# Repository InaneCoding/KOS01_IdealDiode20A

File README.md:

20A 5V-60V Ideal Diode PCB
Ideal Diode circuit based on the Linear Tech LT4359
By Kevin Bibby / http://www.inanecoding.co.uk
----------------------------------------------
v1.0 - 25/02/2017
First version for prototype.
Tested & functional on a basic level (not verified at full current level or behaviour of step response / protections etc).
To be refined for V2 based on things learnt after prototype.
Any comments let me know!

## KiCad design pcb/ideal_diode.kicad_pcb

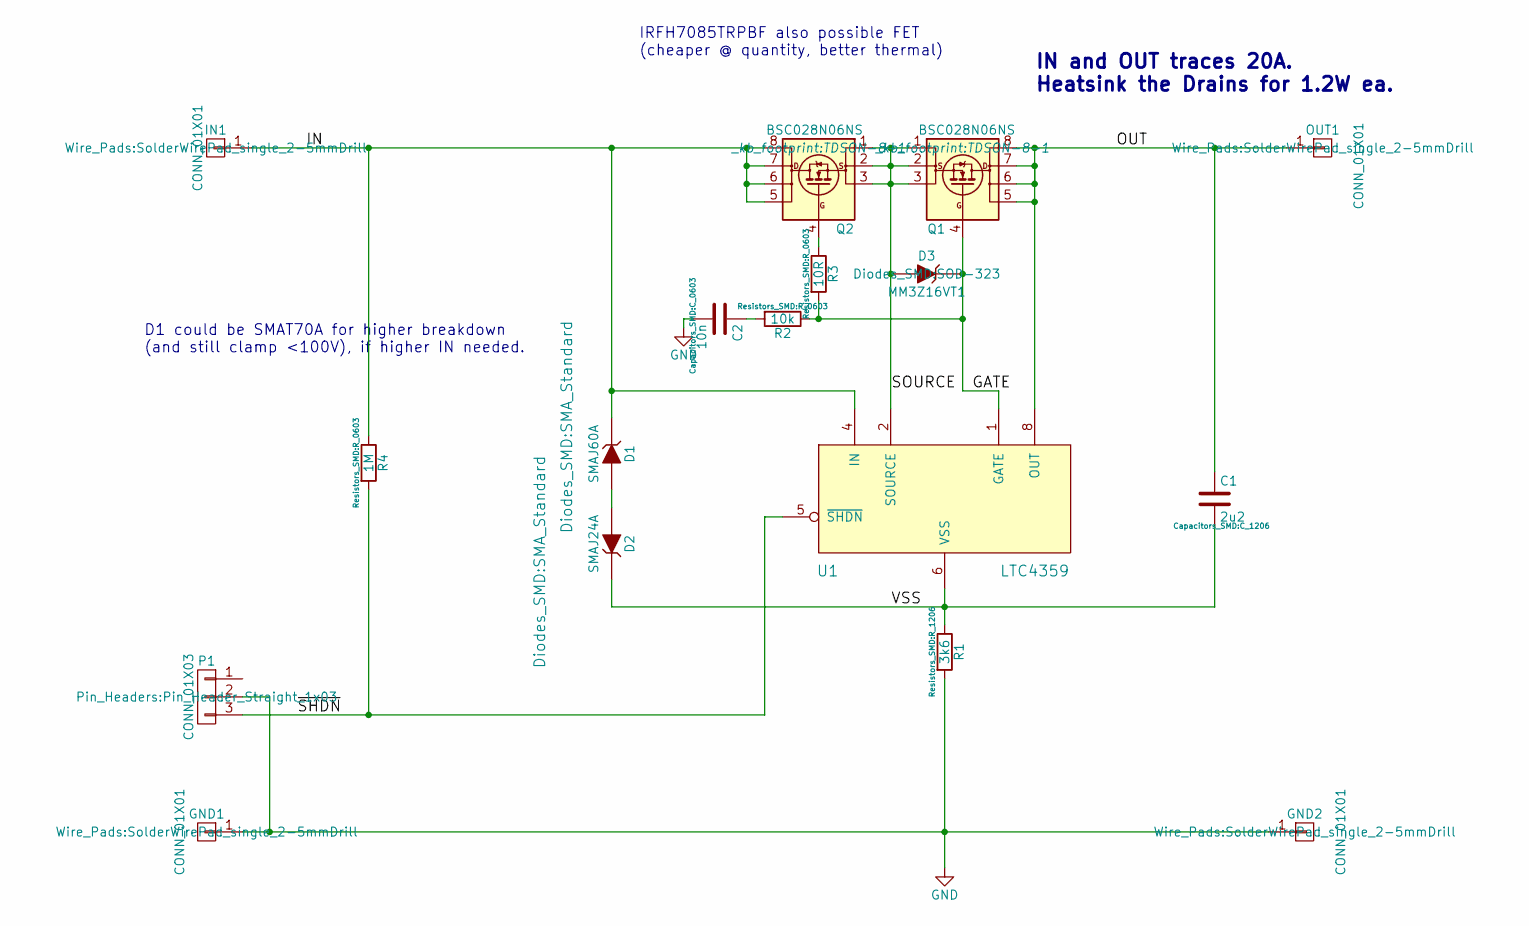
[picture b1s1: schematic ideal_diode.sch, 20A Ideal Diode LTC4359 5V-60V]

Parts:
C1: 2u2; C_1206; ManufacturerPart GRM31CR72A225KA73L
C2: 10n; C_0603; ManufacturerPart 06031C103K4Z2A
D1: SMAJ60A; SMA_Standard; ManufacturerPart SMAJ60A
D2: SMAJ24A; SMA_Standard; ManufacturerPart SMAJ24A
D3: MM3Z16VT1; SOD-323; ManufacturerPart MM3Z16VT1G
GND1, GND2: CONN_01X01; SolderWirePad_single_2-5mmDrill; ManufacturerPart _
IN1: CONN_01X01; SolderWirePad_single_2-5mmDrill; ManufacturerPart _
OUT1: CONN_01X01; SolderWirePad_single_2-5mmDrill; ManufacturerPart _
P1: CONN_01X03; Pin_Header_Straight_1x03; ManufacturerPart M20-9990345
Q1, Q2: BSC028N06NS; TDSON-8-1; ManufacturerPart BSC028N06NS
R1: 3k6; R_1206; ManufacturerPart ERJP08F3601V
R2: 10k; R_0603; ManufacturerPart CRG0603F10K
R3: 10R; R_0603; ManufacturerPart CRG0603F10R
R4: 1M; R_0603; ManufacturerPart CRG0603F1M0
U1: LTC4359; MSOP-8_3x3mm_Pitch0.65mm; ManufacturerPart LTC4359IMS8

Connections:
/GATE: D3.1 (K), Q1.4 (G), R2.1, R3.2, U1.1 (GATE)
/IN: D1.1 (K), IN1.1, Q2.5 (D), Q2.6 (D), Q2.7 (D), Q2.8 (D), R4.1, U1.4 (IN)
/OUT: C1.1, OUT1.1, Q1.5 (D), Q1.6 (D), Q1.7 (D), Q1.8 (D), U1.8 (OUT)
/SOURCE: D3.2 (A), Q1.1 (S), Q1.2 (S), Q1.3 (S), Q2.1 (S), Q2.2 (S), Q2.3 (S), U1.2 (SOURCE)
/VSS: C1.2, D2.1 (K), R1.1, U1.6 (VSS)
/~SHDN: P1.3, R4.2, U1.5 (~SHDN)
GND: C2.2, GND1.1, GND2.1, P1.2, R1.2
unnamed: C2.1, R2.2
unnamed: D1.2 (A), D2.2 (A)
unnamed: Q2.4 (G), R3.1

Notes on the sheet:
IN and OUT traces 20A. Heatsink the Drains for 1.2W ea.
IRFH7085TRPBF also possible FET (cheaper @ quantity, better thermal)
D1 could be SMAT70A for higher breakdown (and still clamp <100V), if higher IN needed.

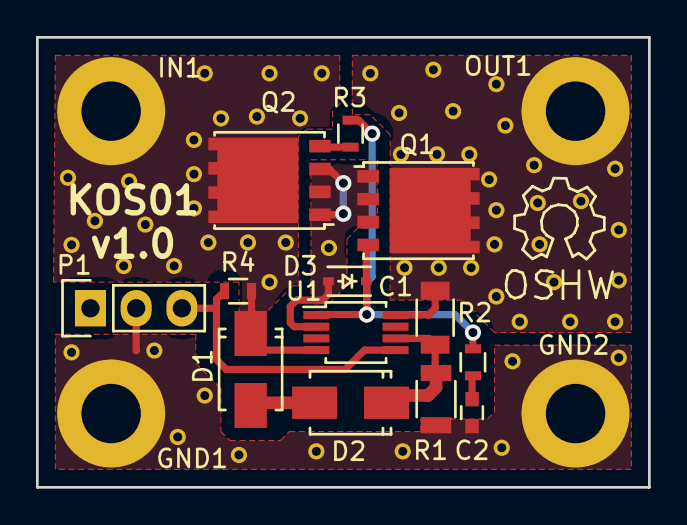
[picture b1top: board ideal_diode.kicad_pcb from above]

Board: 2 copper layers, 34.0 x 25.0 mm, 17 parts (0 on the bottom side), 10 nets.

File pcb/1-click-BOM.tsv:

Reference	Description	Manufacturer	MPN	RS	Value
U1	Ideal Diode Controller MSOP-8	Linear Tech	LTC4359IMS8	8516843	LTC4359
C1	1206 100V X7R 10% Capacitor	Murata	GRM31CR72A225KA73L	8202863	2u2
R1	0.5W 1206 Resistor	Panasonic	ERJP08F3601V	7219866	3k6
Q1	N-Channel 60V 100A TDSON8	Infineon	BSC028N06NS	9064296	BSC028N06NS
D1	60V TVS 400W SMA	Taiwan Semi	SMAJ60A	6873368	SMAJ60A
D2	24V TVS 400W SMA	Taiwan Semi	SMAJ24A	7485161	SMAJ24A
Q2	N-Channel 60V 100A TDSON8	Infineon	BSC028N06NS	9064296	BSC028N06NS
D3	16V 6% 0.2W Zener Diode SOD-323	ON Semi	MM3Z16VT1G	6878212	MM3Z16VT1
R3	0603 Resistor	TE	CRG0603F10R	2132008	10R
R2	0603 Resistor	TE	CRG0603F10K	2132418	10k
C2	0603 100V X7R 10% Capacitor	AVX	06031C103K4Z2A	6983210	10n
R4	0603 Resistor	TE	CRG0603F1M0	2132676	1M
P1	1x3way 2.54mm Header	Harwin	M20-9990345	6812975	CONN_01X03

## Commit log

2016-02-03 initial commit of v1.0 prototype kicad design files & generated gerbers & drill files simulation file for ltspice BOM info incomplete
2016-02-03 added gitignore for .pdf .raw .log files
2016-02-03 added title, date & version numbers to kicad schematic & pcb added *.kicad_pcb-bak *.bak *.net to git ignore
2016-03-05 adding tab-separated version of BOM
2016-03-05 renamed BOM to correct filename for kitnic.it added yaml description for for kitnic
2016-03-05 moving yaml file to root of repo
2016-03-05 made 1-click-BOM lower-case 'C' to match yaml removed ending full stop from tsv line in yaml file
2016-03-05 testing with kitnic... ...copied drill files from drill/ directory to gerbers directory (expected there) ...re-exported board outline with layer alignment target deleted - may be causing issues with 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
2016-03-05 removed layer alignment target from other layers (only did on outline previously) saved in kicad design
2016-12-10 changing to v0.9 ready for tag of version at prototype stage
2016-12-10 setting license as CERN OHL updating titleblocks ready for 1.0 release, added silkscreen ID & version. changed from 4V-70V to 5V-60V to reflect design capabilities changed R1 from 1k to 3k6 & removed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
2017-02-25 last few changes for v1.0 Release Added part info for commodity R's and P1 Re-exported BOM and PCB data after minor changes since proto v0.9 added MPNs to one click BOM Updated readme & TODO, dates &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
2017-02-26 added quantity column needed by kitnic / 1-click-bom
2017-03-02 moved FETs upwards & centred IN/OUT holes to FETs made PCB slightly wider added thermal relief on pads connecting to planes removed extra text from thermal via components so pcb design not cluttered
